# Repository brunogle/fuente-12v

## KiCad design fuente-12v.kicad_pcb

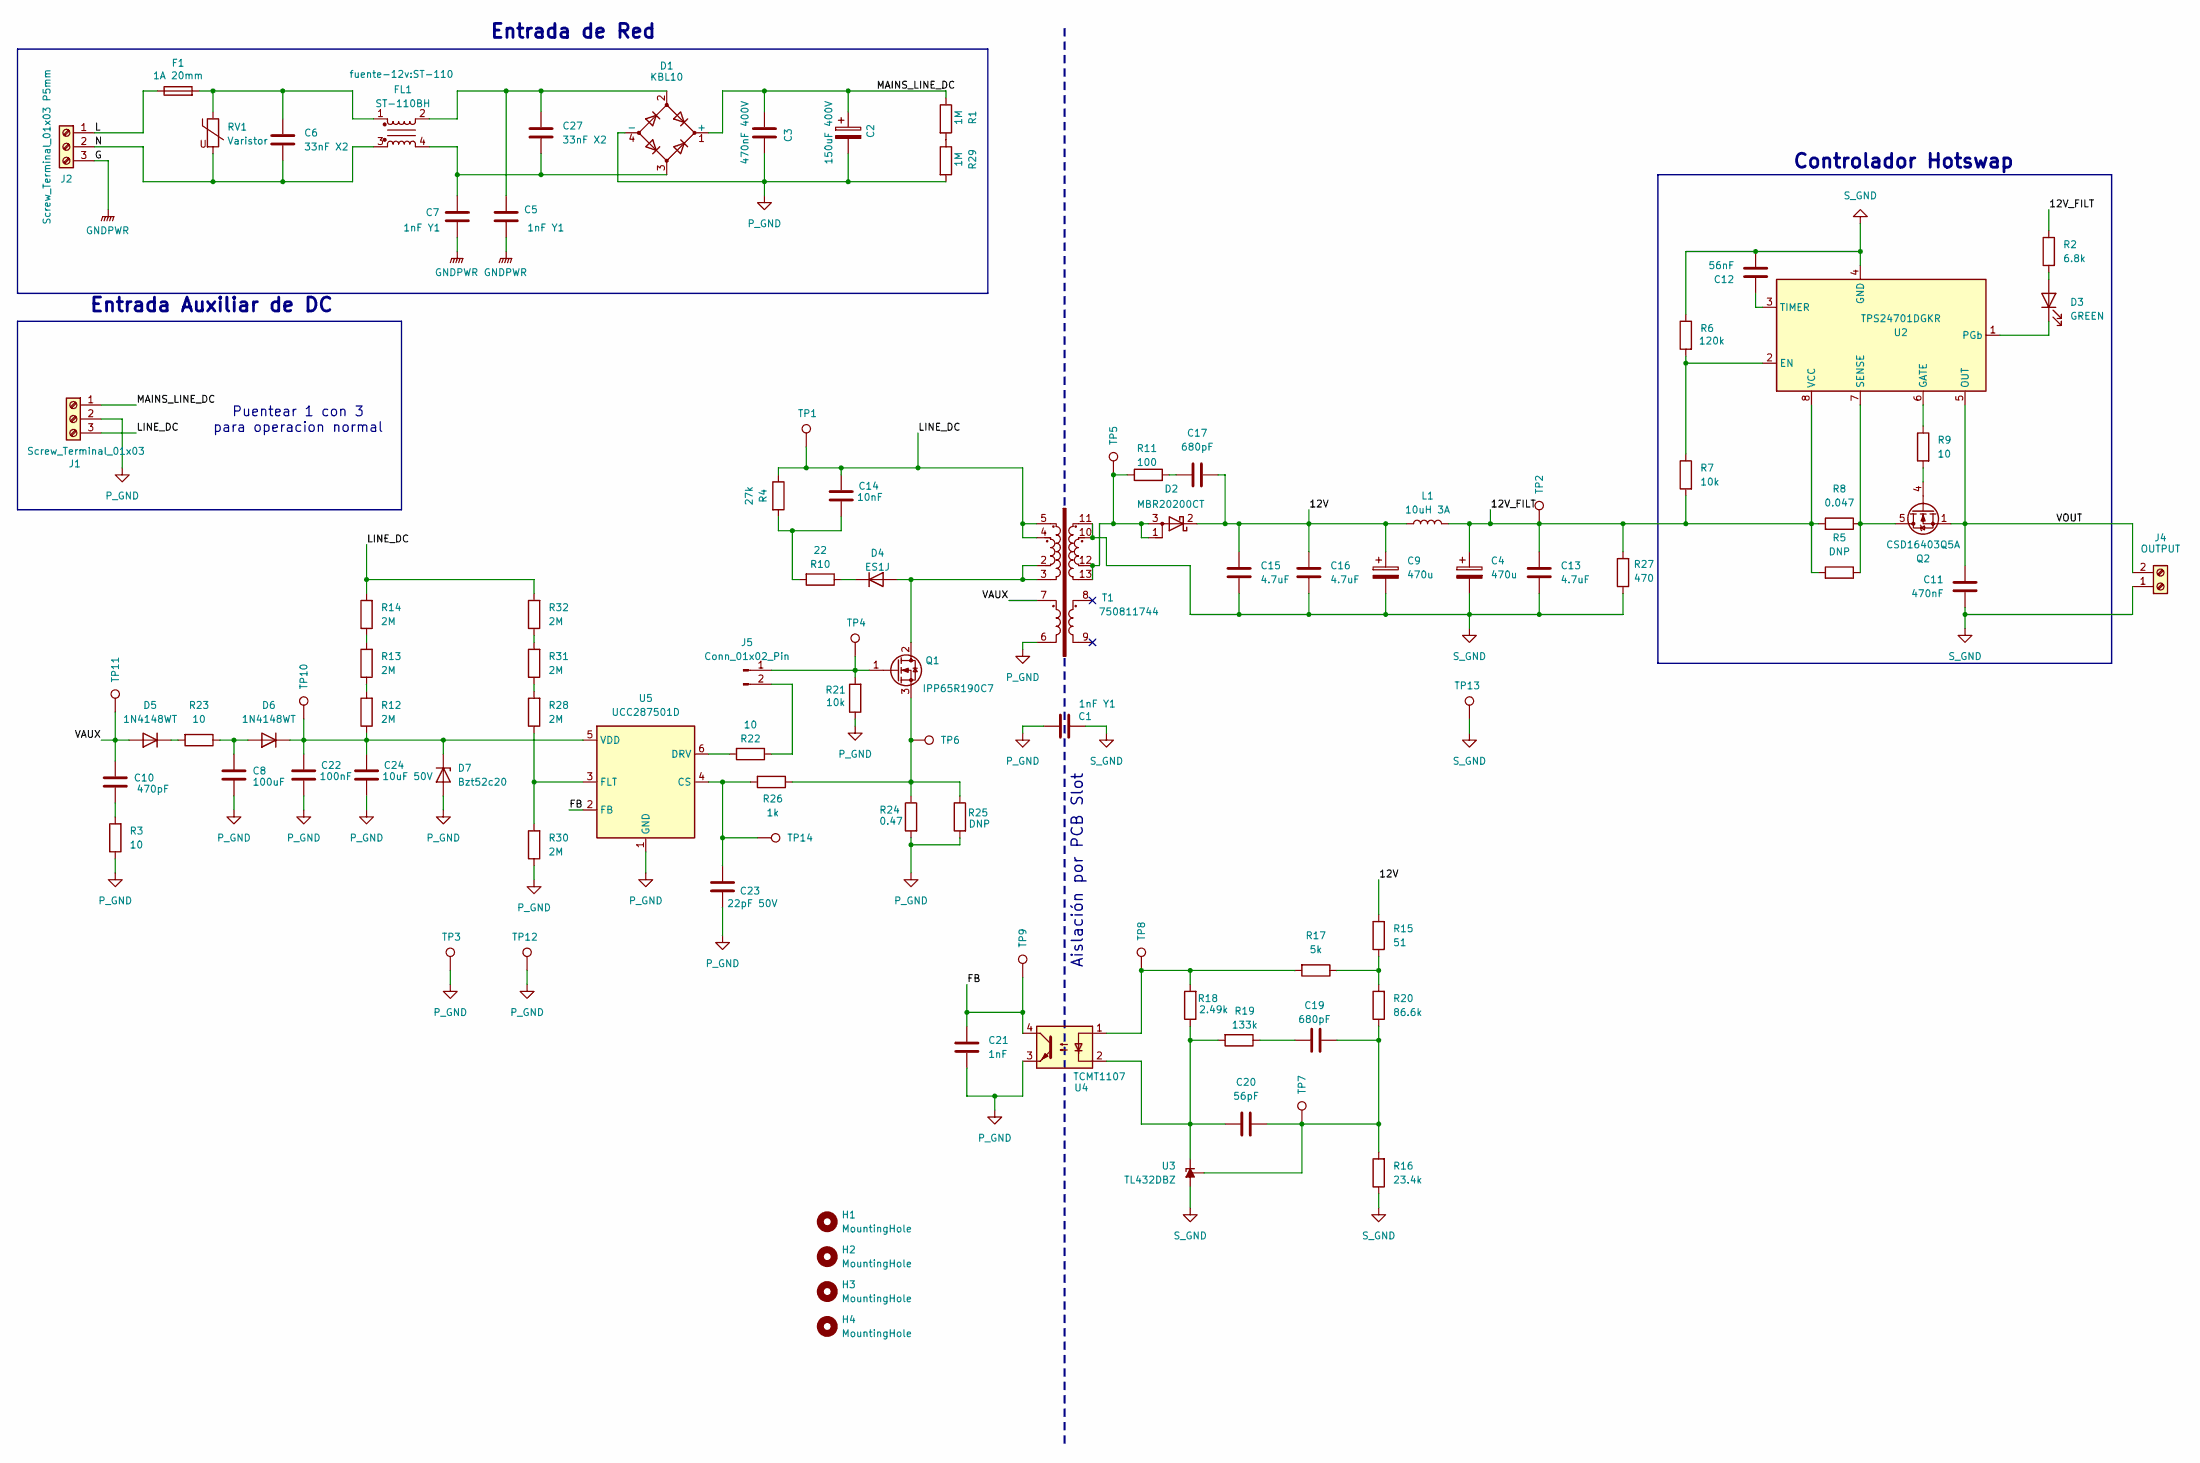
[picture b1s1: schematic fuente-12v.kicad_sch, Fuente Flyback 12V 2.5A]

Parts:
C1: 1nF Y1; C_Disc_D16.0mm_W5.0mm_P10.00mm
C2: 150uF 400V; CP_Radial_D18.0mm_P7.50mm
C3: 470nF 400V; C_Disc_D14.5mm_W5.0mm_P7.50mm
C4, C9: 470u; CP_Radial_D13.0mm_P5.00mm
C5, C7: 1nF Y1; C_Disc_D10.5mm_W5.0mm_P10.00mm
C6, C27: 33nF X2; C_Rect_L11.5mm_W6.6mm_P10.00mm_MKT
C8: 100uF; CP_Radial_D8.0mm_P3.80mm
C10: 470pF; C_0805_2012Metric_Pad1.18x1.45mm_HandSolder
C11: 470nF; C_0805_2012Metric_Pad1.18x1.45mm_HandSolder
C12: 56nF; C_0805_2012Metric_Pad1.18x1.45mm_HandSolder
C13, C15, C16: 4.7uF; C_1206_3216Metric_Pad1.33x1.80mm_HandSolder
C14: 10nF; C_1206_3216Metric_Pad1.33x1.80mm_HandSolder
C17, C19: 680pF; C_0805_2012Metric_Pad1.18x1.45mm_HandSolder
C20: 56pF; C_0805_2012Metric_Pad1.18x1.45mm_HandSolder
C21: 1nF; C_0805_2012Metric_Pad1.18x1.45mm_HandSolder
C22: 100nF; C_0805_2012Metric_Pad1.18x1.45mm_HandSolder
C23: 22pF 50V; C_0805_2012Metric_Pad1.18x1.45mm_HandSolder
C24: 10uF 50V; C_0805_2012Metric_Pad1.18x1.45mm_HandSolder
D1: KBL10; Diode_Bridge_Vishay_KBL
D2: MBR20200CT; TO-220-3_Vertical
D3: GREEN; LED_0805_2012Metric_Pad1.15x1.40mm_HandSolder
D4: ES1J; D_SMA_Handsoldering
D5, D6: 1N4148WT; D_SOD-323_HandSoldering
D7: Bzt52c20; Nexperia_CFP3_SOD-123W
F1: 1A 20mm; Fuseholder_BLX-A
FL1: ST-110BH; ST-110
H1, H2, H3, H4: MountingHole; MountingHole_4.3mm_M4_DIN965
J1: Screw_Terminal_01x03; TerminalBlock_MaiXu_MX126-5.0-03P_1x03_P5.00mm
J2: Screw_Terminal_01x03 P5mm; TerminalBlock_MaiXu_MX126-5.0-03P_1x03_P5.00mm
J4: OUTPUT; TerminalBlock_MaiXu_MX126-5.0-02P_1x02_P5.00mm
J5: Conn_01x02_Pin; PinHeader_1x02_P2.54mm_Vertical
L1: 10uH 3A; L_Toroid_Vertical_L16.0mm_W8.0mm_P7.62mm
Q1: IPP65R190C7; TO-220-3_Vertical
Q2: CSD16403Q5A; TDSON-8-1
R1, R29: 1M; R_1206_3216Metric_Pad1.30x1.75mm_HandSolder
R2: 6.8k; R_0805_2012Metric_Pad1.20x1.40mm_HandSolder
R3, R9, R22, R23: 10; R_0805_2012Metric_Pad1.20x1.40mm_HandSolder
R4: 27k; R_Axial_DIN0411_L9.9mm_D3.6mm_P15.24mm_Horizontal
R5, R25: DNP; R_2512_6332Metric_Pad1.40x3.35mm_HandSolder
R6: 120k; R_0805_2012Metric_Pad1.20x1.40mm_HandSolder
R7, R21: 10k; R_0805_2012Metric_Pad1.20x1.40mm_HandSolder
R8: 0.047; R_2512_6332Metric_Pad1.40x3.35mm_HandSolder
R10: 22; R_1206_3216Metric_Pad1.30x1.75mm_HandSolder
R11: 100; R_0805_2012Metric_Pad1.20x1.40mm_HandSolder
R12, R13, R14, R28, R30, R31, R32: 2M; R_0805_2012Metric_Pad1.20x1.40mm_HandSolder
R15: 51; R_0805_2012Metric_Pad1.20x1.40mm_HandSolder
R16: 23.4k; R_0805_2012Metric_Pad1.20x1.40mm_HandSolder
R17: 5k; R_0805_2012Metric_Pad1.20x1.40mm_HandSolder
R18: 2.49k; R_0805_2012Metric_Pad1.20x1.40mm_HandSolder
R19: 133k; R_0805_2012Metric_Pad1.20x1.40mm_HandSolder
R20: 86.6k; R_0805_2012Metric_Pad1.20x1.40mm_HandSolder
R24: 0.47; R_2512_6332Metric_Pad1.40x3.35mm_HandSolder
R26: 1k; R_0805_2012Metric_Pad1.20x1.40mm_HandSolder
R27: 470; R_0805_2012Metric_Pad1.20x1.40mm_HandSolder
RV1: Varistor; C_Disc_D8.0mm_W2.5mm_P5.00mm
T1: 750811744
TP1, TP2, TP3, TP4, TP5, TP6, TP7, TP8, TP9, TP10, TP11, TP12, TP13, TP14: TestPoint; PinHeader_1x01_P2.54mm_Vertical
U2: TPS24701DGKR; Texas_S-PDSO-G8_3x3mm_P0.65mm
U3: TL432DBZ; SOT-23W_Handsoldering
U4: TCMT1107; SOP-4_4.4x2.6mm_P1.27mm
U5: UCC287501D; TSOT-23-6_HandSoldering

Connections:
/12V: C9.1, C15.2, C16.2, C17.2, D2.2 (K), L1.1, R15.2
/12V_FILT: C4.1, C13.2, L1.2, R2.1, R5.2, R7.2, R8.2, R27.2, TP2.1, U2.8 (VCC)
/FB: C21.2, TP9.1, U4.4, U5.2 (FB)
/L: F1.1, J2.1
/LINE_DC: C14.1, J1.3, R4.1, R14.2, R32.2, T1.4, T1.5, TP1.1
/MAINS_LINE_DC: C2.1, C3.1, D1.1 (+), J1.1, R1.1
/N: C6.1, FL1.3, J2.2, RV1.2
/VAUX: C10.1, D5.2 (A), T1.7, TP11.1
/VOUT: C11.2, J4.2, Q2.1 (S), Q2.2 (S), Q2.3 (S), U2.5 (OUT)
GNDPWR: C5.2, C7.1, J2.3
unnamed: C6.2, F1.2, FL1.1, RV1.1
unnamed: C10.2, R3.2
unnamed: C14.2, R4.2, R10.2
unnamed: C17.1, R11.2
unnamed: C19.2, R19.1
unnamed: C7.2, C27.1, D1.3, FL1.4
unnamed: C5.1, C27.2, D1.2, FL1.2
unnamed: D2.1 (A), D2.3 (A), R11.1, T1.12, T1.13, TP5.1
unnamed: D3.2 (A), R2.2
unnamed: D3.1 (K), U2.1 (PGb)
unnamed: D4.2 (A), Q1.2 (D), T1.2, T1.3
unnamed: D4.1 (K), R10.1
unnamed: D5.1 (K), R23.2
unnamed: C8.1, D6.2 (A), R23.1
unnamed: C22.1, C24.1, D6.1 (K), D7.1 (K), R12.1, TP10.1, U5.5 (VDD)
unnamed: J5.1, Q1.1 (G), R21.2, TP4.1
unnamed: J5.2, R22.1
unnamed: Q1.3 (S), R24.1, R25.1, R26.1, TP6.1
unnamed: Q2.5 (D), R5.1, R8.1, U2.7 (SENSE)
unnamed: Q2.4 (G), R9.2
unnamed: R1.2, R29.1
unnamed: R12.2, R13.1
unnamed: R13.2, R14.1
unnamed: R15.1, R17.1, R20.2
unnamed: R17.2, R18.2, TP8.1, U4.1
unnamed: R28.2, R31.1
unnamed: R31.2, R32.1
unnamed: R6.2, R7.1, U2.2 (EN)
unnamed: R9.1, U2.6 (GATE)
unnamed: C12.2, U2.3 (TIMER)
unnamed: C20.2, R18.1, R19.2, U3.2 (K), U4.2
unnamed: C19.1, C20.1, R16.2, R20.1, TP7.1, U3.1 (REF)
unnamed: C23.2, R26.2, TP14.1, U5.4 (CS)
unnamed: R22.2, U5.6 (DRV)
unnamed: R28.1, R30.2, U5.3 (FLT)
P_GND: C1.2, C2.2, C3.2, C8.2, C21.1, C22.2, C23.1, C24.2, D1.4 (-), D7.2 (A), J1.2, R3.1, R21.1, R24.2, R25.2, R29.2, R30.1, T1.6, TP3.1, TP12.1, U4.3, U5.1 (GND)
S_GND: C1.1, C4.2, C9.2, C11.1, C12.1, C13.1, C15.1, C16.1, J4.1, R6.1, R16.1, R27.1, T1.10, T1.11, TP13.1, U2.4 (GND), U3.3 (A)

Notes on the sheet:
Aislación por PCB Slot
Puentear 1 con 3 para operacion normal
Entrada de Red
Controlador Hotswap
Entrada Auxiliar de DC

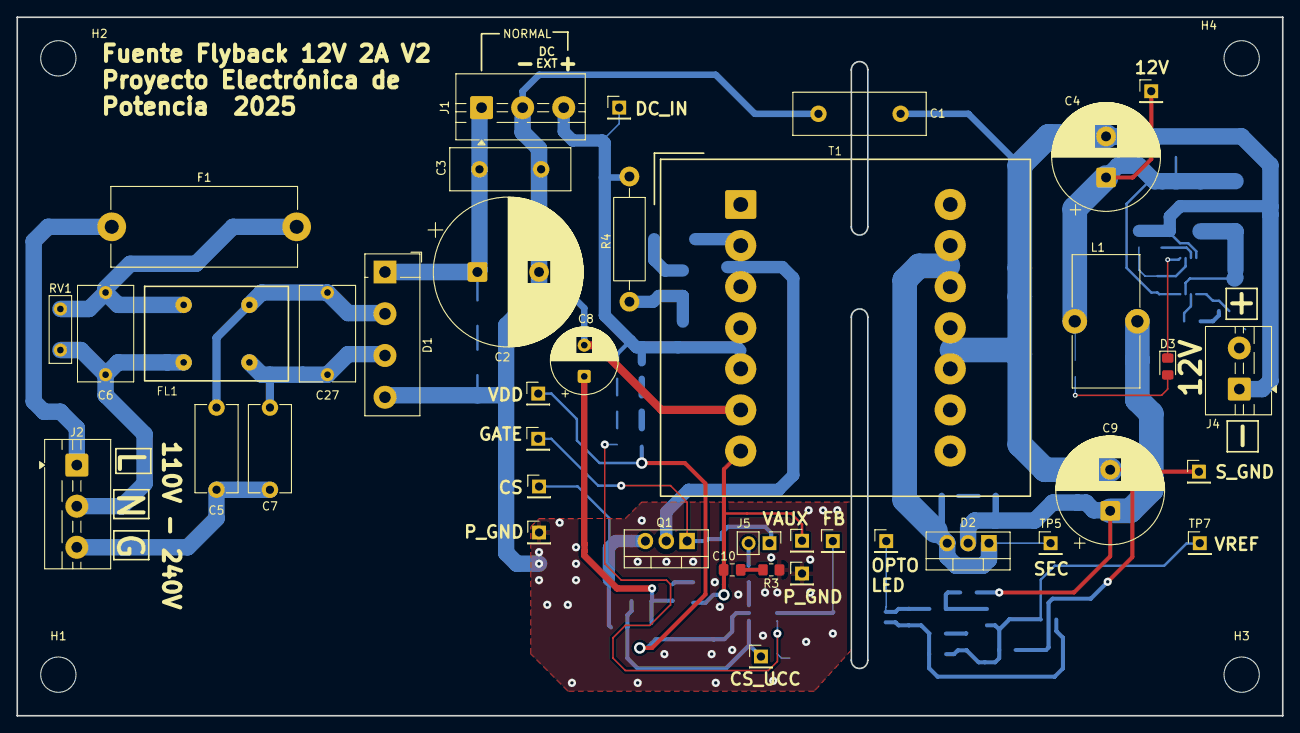
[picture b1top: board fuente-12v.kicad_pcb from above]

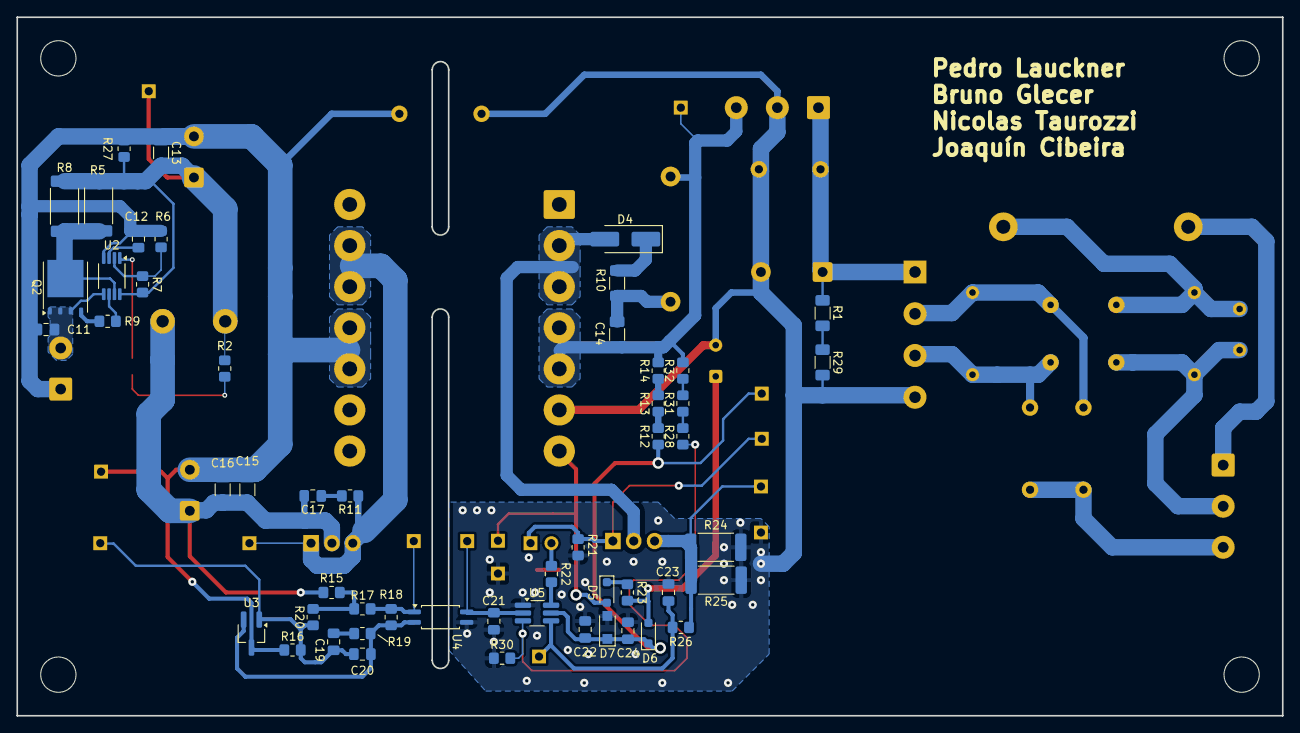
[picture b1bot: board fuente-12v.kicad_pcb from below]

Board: 2 copper layers, 154.0 x 85.0 mm, 96 parts (52 on the bottom side), 47 nets.

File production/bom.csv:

Designator,Footprint,Quantity,Value,LCSC Part #
C10,0805,1,470pF,
C11,0805,1,470nF,
C12,0805,1,56nF,
"C13, C15, C16",1206,3,4.7uF,
C14,1206,1,10nF,
"C17, C19",0805,2,680pF,
C20,0805,1,56pF,
C21,0805,1,1nF,
C22,0805,1,100nF,
C23,0805,1,22pF 50V,
C24,0805,1,10uF 50V,
D3,0805,1,GREEN,
D4,D_SMA_Handsoldering,1,ES1J,
"D5, D6",D_SOD-323_HandSoldering,2,1N4148WT,
D7,Nexperia_CFP3_SOD-123W,1,Bzt52c20,
J5,PinHeader_1x02_P2.54mm_Vertical,1,Conn_01x02_Pin,
Q2,TDSON-8-1,1,CSD16403Q5A,
R10,1206,1,22,
R11,0805,1,100,
"R12, R13, R14, R28, R30, R31, R32",0805,7,2M,
R15,0805,1,51,
R16,0805,1,23.4k,
R17,0805,1,5k,
R18,0805,1,2.49k,
R19,0805,1,133k,
R2,0805,1,6.8k,
R20,0805,1,86.6k,
"R21, R7",0805,2,10k,
"R22, R23, R3, R9",0805,4,10,
R24,2512,1,0.47,
"R25, R5",2512,2,DNP,
R26,0805,1,1k,
R27,0805,1,470,
R4,R_Axial_DIN0411_L9.9mm_D3.6mm_P15.24mm_Horizontal,1,27k,
R6,0805,1,120k,
R8,2512,1,0.047,
U2,Texas_S-PDSO-G8_3x3mm_P0.65mm,1,TPS24701DGKR,
U3,SOT-23W_Handsoldering,1,TL432DBZ,
U5,TSOT-23-6_HandSoldering,1,UCC287501D,

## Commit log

2025-08-25 Started schematic
2025-10-06 Esquematico completo y PCB routeado
2025-10-06 Fixes
2025-10-09 Terminada. Necesita revision
2025-10-09 Version enviada a JLCPCB
2026-01-23 V2 routeada por bruno, necesita revision
2026-02-03 Correcciones en el esquemático
2026-02-04 Cambios v2
2026-02-05 V2 fabricada
